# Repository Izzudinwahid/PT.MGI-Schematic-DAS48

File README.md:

# PT.MGI-Schematic-DAS48
Rangkaian Device Alert System 48 Channel 110v

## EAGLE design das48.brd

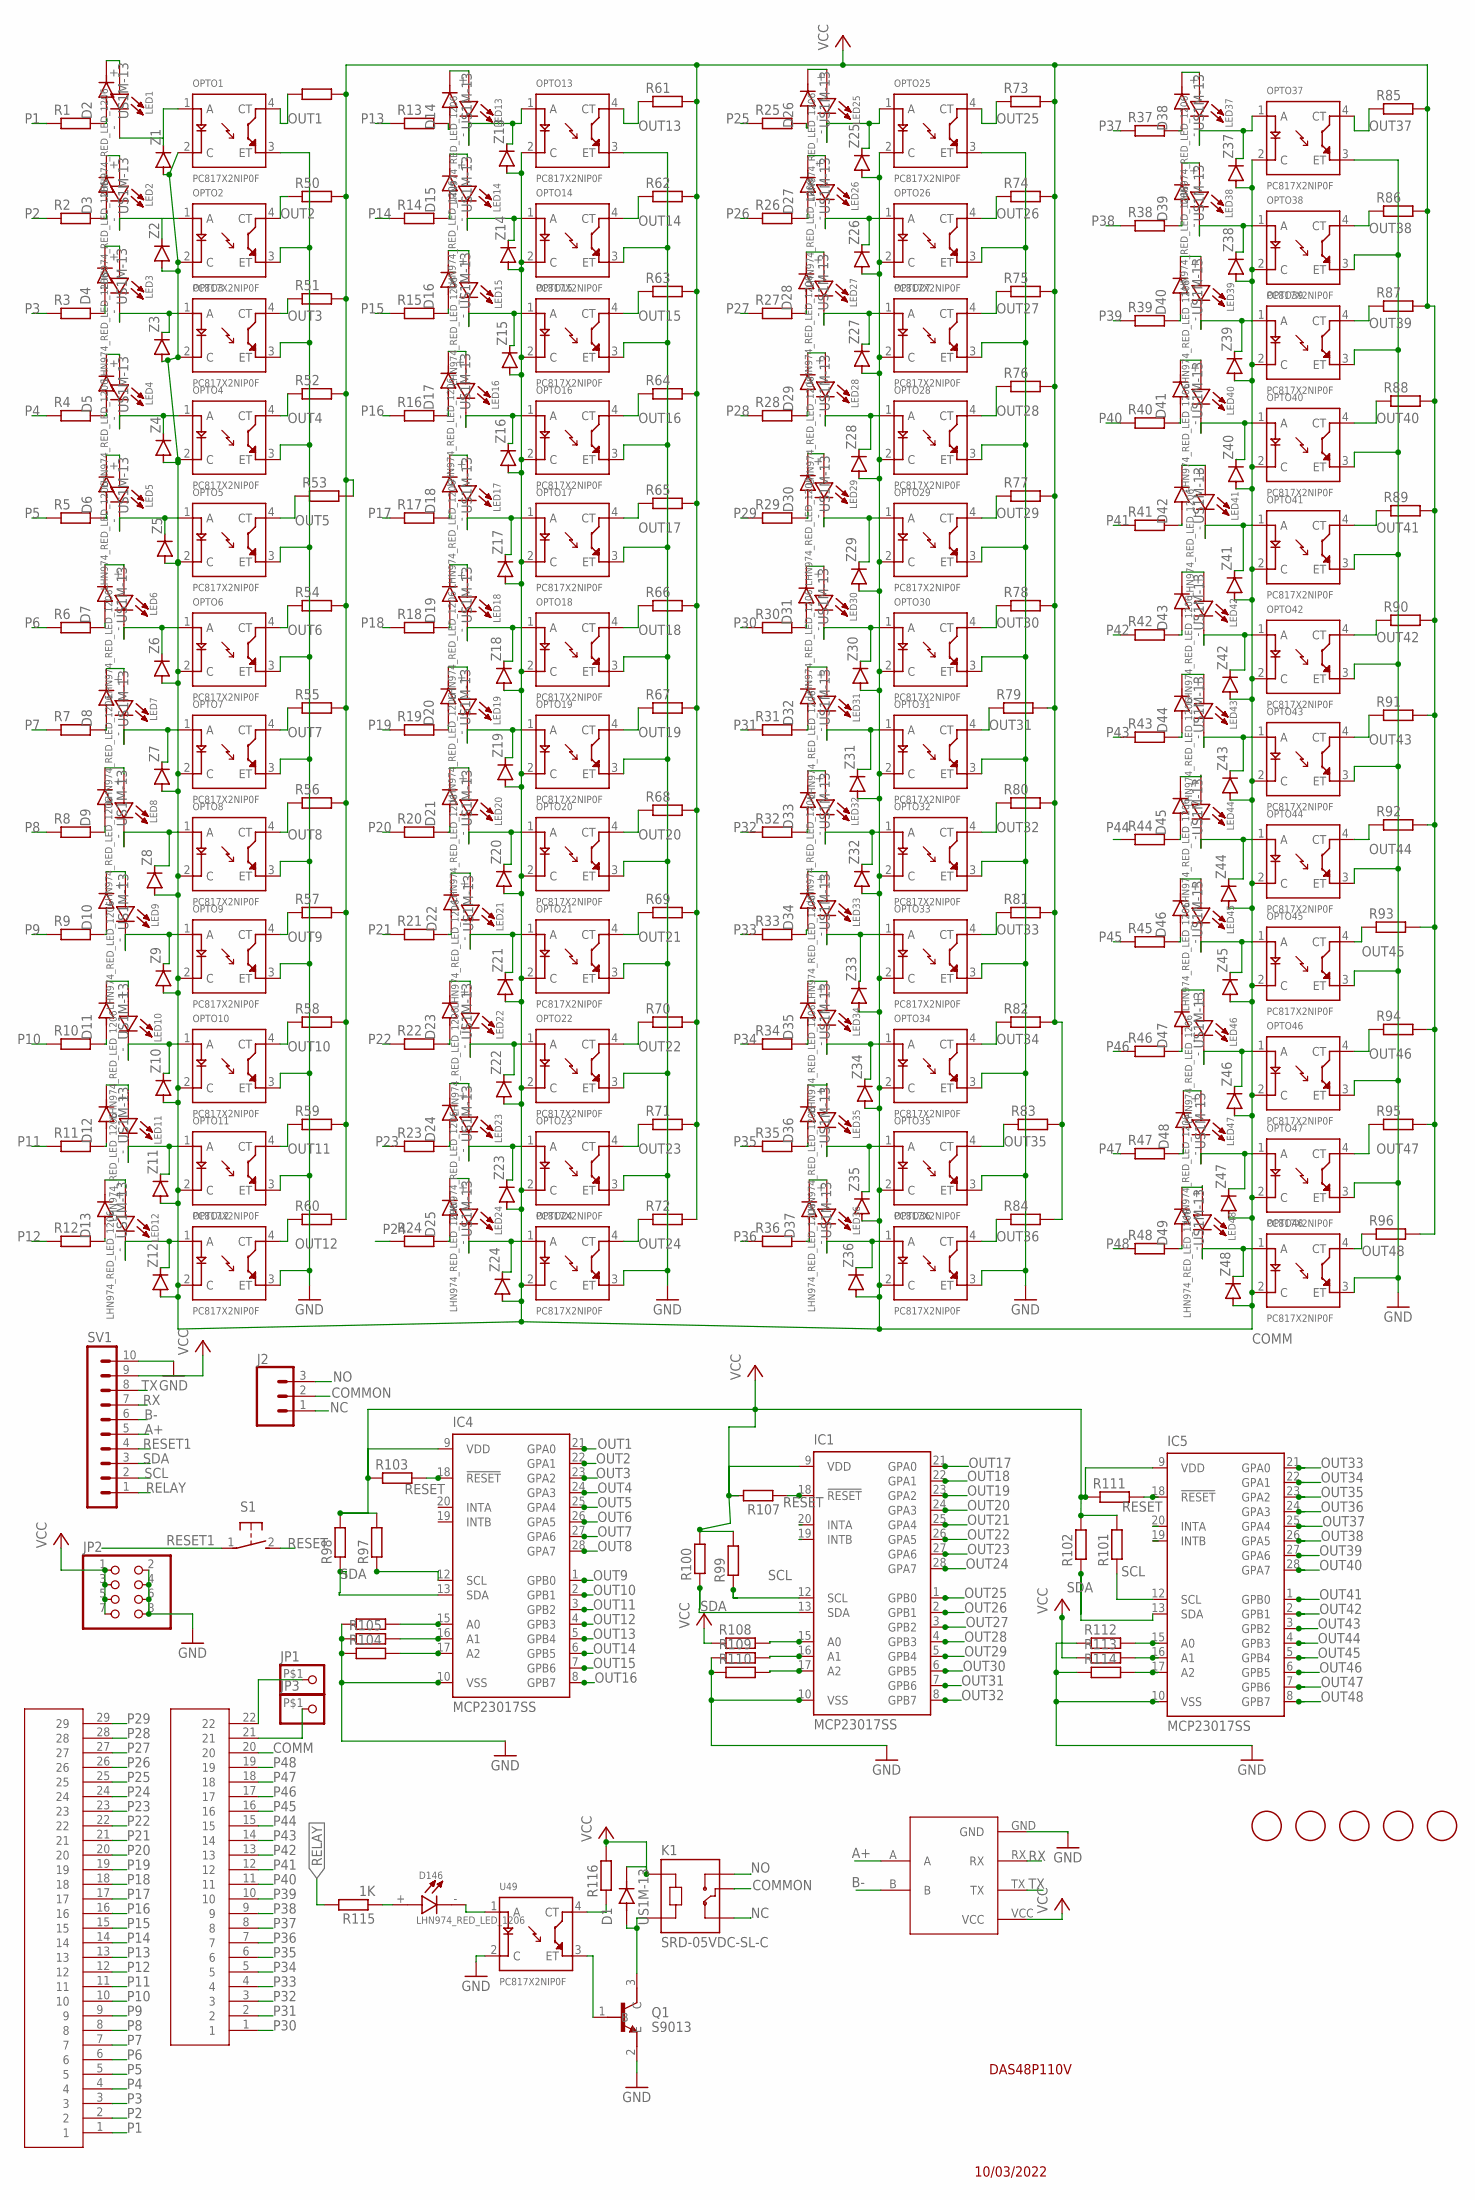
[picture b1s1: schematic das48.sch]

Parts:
D1, D2, D3, D4, D5, D6, D7, D8, D9, D10, D11, D12, D13, D14, D15, D16, D17, D18, D19, D20, D21, D22, D23, D24, D25, D26, D27, D28, D29, D30, D31, D32, D33, D34, D35, D36, D37, D38, D39, D40, D41, D42, D43, D44, D45, D46, D47, D48, D49: US1M-13; DIOM5226X240N
D146: LHN974_RED_LED_1206; LEDC3216X120N
HEADER-22P1: HEADER-22P; HEADER-29P
HEADER-29P1: HEADER-29P
IC1, IC4, IC5: MCP23017SS; SSOP28DB
J2: CONN_03LONGPADS; 1X03_LONGPADS
JP1, JP3: PINHD-1X1-BIGPOGO; 1X1-BIGPOGO
JP2: PINHD-2X4; 2X04
K1: SRD-05VDC-SL-C; RELAY_SRD-05VDC-SL-C
LED1, LED2, LED3, LED4, LED5, LED6, LED7, LED8, LED9, LED10, LED11, LED12, LED13, LED14, LED15, LED16, LED17, LED18, LED19, LED20, LED21, LED22, LED23, LED24, LED25, LED26, LED27, LED28, LED29, LED30, LED31, LED32, LED33, LED34, LED35, LED36, LED37, LED38, LED39, LED40, LED41, LED42, LED43, LED44, LED45, LED46, LED47, LED48: LHN974_RED_LED_1206; LEDC3216X120N
OPTO1, OPTO2, OPTO3, OPTO4, OPTO5, OPTO6, OPTO7, OPTO8, OPTO9, OPTO10, OPTO11, OPTO12, OPTO13, OPTO14, OPTO15, OPTO16, OPTO17, OPTO18, OPTO19, OPTO20, OPTO21, OPTO22, OPTO23, OPTO24, OPTO25, OPTO26, OPTO27, OPTO28, OPTO29, OPTO30, OPTO31, OPTO32, OPTO33, OPTO34, OPTO35, OPTO36, OPTO37, OPTO38, OPTO39, OPTO40, OPTO41, OPTO42, OPTO43, OPTO44, OPTO45, OPTO46, OPTO47, OPTO48: PC817X2NIP0F; SOT254P975X400-4N
Q1: S9013; SOT95P240X120-3N
R1, R2, R3, R4, R5, R6, R7, R8, R9, R10, R11, R12, R13, R14, R15, R16, R17, R18, R19, R20, R21, R22, R23, R24, R25, R26, R27, R28, R29, R30, R31, R32, R33, R34, R35, R36, R37, R38, R39, R40, R41, R42, R43, R44, R45, R46, R47, R48: R-EU_0617/17; 0617/17
R49, R50, R51, R52, R53, R54, R55, R56, R57, R58, R59, R60, R61, R62, R63, R64, R65, R66, R67, R68, R69, R70, R71, R72, R73, R74, R75, R76, R77, R78, R79, R80, R81, R82, R83, R84, R85, R86, R87, R88, R89, R90, R91, R92, R93, R94, R95, R96, R97, R98, R99, R100, R101, R102, R103, R104, R105, R106, R107, R108, R109, R110, R111, R112, R113, R114, R116: R-EU_R0805; R0805
R115: 1K; R0805
S1: 31-XX; B3F-31XX
SV1: MA10-1
TTL-RS1: TTL-RS485
U49: PC817X2NIP0F; SOT254P975X400-4N
U$1, U$2, U$3, U$4, U$5: FIDUCIAL; FIDUCIAL_1MM
Z1, Z2, Z3, Z4, Z5, Z6, Z7, Z8, Z9, Z10, Z11, Z12, Z13, Z14, Z15, Z16, Z17, Z18, Z19, Z20, Z21, Z22, Z23, Z24, Z25, Z26, Z27, Z28, Z29, Z30, Z31, Z32, Z33, Z34, Z35, Z36, Z37, Z38, Z39, Z40, Z41, Z42, Z43, Z44, Z45, Z46, Z47, Z48: DIODE-SOD123; SOD123

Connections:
A+: SV1.5, TTL-RS1.A
B-: SV1.6, TTL-RS1.B
COMM: HEADER-22P1.20, OPTO1.2 (C), OPTO2.2 (C), OPTO3.2 (C), OPTO4.2 (C), OPTO5.2 (C), OPTO6.2 (C), OPTO7.2 (C), OPTO8.2 (C), OPTO9.2 (C), OPTO10.2 (C), OPTO11.2 (C), OPTO12.2 (C), OPTO13.2 (C), OPTO14.2 (C), OPTO15.2 (C), OPTO16.2 (C), OPTO17.2 (C), OPTO18.2 (C), OPTO19.2 (C), OPTO20.2 (C), OPTO21.2 (C), OPTO22.2 (C), OPTO23.2 (C), OPTO24.2 (C), OPTO25.2 (C), OPTO26.2 (C), OPTO27.2 (C), OPTO28.2 (C), OPTO29.2 (C), OPTO30.2 (C), OPTO31.2 (C), OPTO32.2 (C), OPTO33.2 (C), OPTO34.2 (C), OPTO35.2 (C), OPTO36.2 (C), OPTO37.2 (C), OPTO38.2 (C), OPTO39.2 (C), OPTO40.2 (C), OPTO41.2 (C), OPTO42.2 (C), OPTO43.2 (C), OPTO44.2 (C), OPTO45.2 (C), OPTO46.2 (C), OPTO47.2 (C), OPTO48.2 (C), Z1.A, Z2.A, Z3.A, Z4.A, Z5.A, Z6.A, Z7.A, Z8.A, Z9.A, Z10.A, Z11.A, Z12.A, Z13.A, Z14.A, Z15.A, Z16.A, Z17.A, Z18.A, Z19.A, Z20.A, Z21.A, Z22.A, Z23.A, Z24.A, Z25.A, Z26.A, Z27.A, Z28.A, Z29.A, Z30.A, Z31.A, Z32.A, Z33.A, Z34.A, Z35.A, Z36.A, Z37.A, Z38.A, Z39.A, Z40.A, Z41.A, Z42.A, Z43.A, Z44.A, Z45.A, Z46.A, Z47.A, Z48.A
COMMON: J2.2, K1.COM
GND: IC1.10 (VSS), IC4.10 (VSS), IC5.10 (VSS), JP2.2, JP2.4, JP2.6, JP2.8, OPTO1.3 (ET), OPTO2.3 (ET), OPTO3.3 (ET), OPTO4.3 (ET), OPTO5.3 (ET), OPTO6.3 (ET), OPTO7.3 (ET), OPTO8.3 (ET), OPTO9.3 (ET), OPTO10.3 (ET), OPTO11.3 (ET), OPTO12.3 (ET), OPTO13.3 (ET), OPTO14.3 (ET), OPTO15.3 (ET), OPTO16.3 (ET), OPTO17.3 (ET), OPTO18.3 (ET), OPTO19.3 (ET), OPTO20.3 (ET), OPTO21.3 (ET), OPTO22.3 (ET), OPTO23.3 (ET), OPTO24.3 (ET), OPTO25.3 (ET), OPTO26.3 (ET), OPTO27.3 (ET), OPTO28.3 (ET), OPTO29.3 (ET), OPTO30.3 (ET), OPTO31.3 (ET), OPTO32.3 (ET), OPTO33.3 (ET), OPTO34.3 (ET), OPTO35.3 (ET), OPTO36.3 (ET), OPTO37.3 (ET), OPTO38.3 (ET), OPTO39.3 (ET), OPTO40.3 (ET), OPTO41.3 (ET), OPTO42.3 (ET), OPTO43.3 (ET), OPTO44.3 (ET), OPTO45.3 (ET), OPTO46.3 (ET), OPTO47.3 (ET), OPTO48.3 (ET), Q1.2 (E), R104.1, R105.1, R106.1, R109.1, R110.1, R112.1, R114.1, SV1.10, TTL-RS1.GND, U49.2 (C)
unnamed: D2.A, R1.2
unnamed: D2.C (K), LED1.+
unnamed: D3.A, R2.2
unnamed: D3.C (K), LED2.+
unnamed: D4.A, R3.2
unnamed: D4.C (K), LED3.+
unnamed: D5.A, R4.2
unnamed: D5.C (K), LED4.+
unnamed: D6.A, R5.2
unnamed: D6.C (K), LED5.+
unnamed: D7.A, R6.2
unnamed: D7.C (K), LED6.+
unnamed: D8.A, R7.2
unnamed: D8.C (K), LED7.+
unnamed: D9.A, R8.2
unnamed: D9.C (K), LED8.+
unnamed: D15.A, R14.2
unnamed: LED1.-, OPTO1.1 (A), Z1.C
unnamed: LED13.-, OPTO13.1 (A), Z13.C
unnamed: D10.A, R9.2
unnamed: LED14.-, OPTO14.1 (A), Z14.C
unnamed: D10.C (K), LED9.+
unnamed: LED15.-, OPTO15.1 (A), Z15.C
unnamed: D11.A, R10.2
unnamed: LED16.-, OPTO16.1 (A), Z16.C
unnamed: D11.C (K), LED10.+
unnamed: LED17.-, OPTO17.1 (A), Z17.C
unnamed: D12.A, R11.2
unnamed: LED18.-, OPTO18.1 (A), Z18.C
unnamed: D12.C (K), LED11.+
unnamed: LED19.-, OPTO19.1 (A), Z19.C
unnamed: LED20.-, OPTO20.1 (A), Z20.C
unnamed: LED21.-, OPTO21.1 (A), Z21.C
unnamed: D15.C (K), LED14.+
unnamed: LED22.-, OPTO22.1 (A), Z22.C
unnamed: D13.A, R12.2
unnamed: LED23.-, OPTO23.1 (A), Z23.C
unnamed: D13.C (K), LED12.+
unnamed: LED24.-, OPTO24.1 (A), Z24.C
unnamed: D14.A, R13.2
unnamed: LED25.-, OPTO25.1 (A), Z25.C
unnamed: D14.C (K), LED13.+
unnamed: LED26.-, OPTO26.1 (A), Z26.C
unnamed: D16.A, R15.2
unnamed: LED27.-, OPTO27.1 (A), Z27.C
unnamed: D16.C (K), LED15.+
unnamed: LED28.-, OPTO28.1 (A), Z28.C
unnamed: D17.A, R16.2
unnamed: LED29.-, OPTO29.1 (A), Z29.C
unnamed: D17.C (K), LED16.+
unnamed: LED30.-, OPTO30.1 (A), Z30.C
unnamed: D18.A, R17.2
unnamed: LED31.-, OPTO31.1 (A), Z31.C
unnamed: D18.C (K), LED17.+
unnamed: LED32.-, OPTO32.1 (A), Z32.C
unnamed: D19.A, R18.2
unnamed: LED33.-, OPTO33.1 (A), Z33.C
unnamed: D19.C (K), LED18.+
unnamed: LED34.-, OPTO34.1 (A), Z34.C
unnamed: D20.A, R19.2
unnamed: LED35.-, OPTO35.1 (A), Z35.C
unnamed: D20.C (K), LED19.+
unnamed: LED36.-, OPTO36.1 (A), Z36.C
unnamed: D32.A, R31.2
unnamed: LED37.-, OPTO37.1 (A), Z37.C
unnamed: D21.A, R20.2
unnamed: LED38.-, OPTO38.1 (A), Z38.C
unnamed: D21.C (K), LED20.+
unnamed: LED39.-, OPTO39.1 (A), Z39.C
unnamed: LED40.-, OPTO40.1 (A), Z40.C
unnamed: D22.A, R21.2
unnamed: LED41.-, OPTO41.1 (A), Z41.C
unnamed: D22.C (K), LED21.+
unnamed: LED42.-, OPTO42.1 (A), Z42.C
unnamed: LED43.-, OPTO43.1 (A), Z43.C
unnamed: D23.A, R22.2
unnamed: LED44.-, OPTO44.1 (A), Z44.C
unnamed: D23.C (K), LED22.+
unnamed: LED45.-, OPTO45.1 (A), Z45.C
unnamed: D24.A, R23.2
unnamed: LED46.-, OPTO46.1 (A), Z46.C
unnamed: D24.C (K), LED23.+
unnamed: LED47.-, OPTO47.1 (A), Z47.C
unnamed: D25.A, R24.2
unnamed: LED48.-, OPTO48.1 (A), Z48.C
unnamed: LED2.-, OPTO2.1 (A), Z2.C
unnamed: LED3.-, OPTO3.1 (A), Z3.C
unnamed: LED4.-, OPTO4.1 (A), Z4.C
unnamed: LED5.-, OPTO5.1 (A), Z5.C
unnamed: LED6.-, OPTO6.1 (A), Z6.C
unnamed: LED7.-, OPTO7.1 (A), Z7.C
unnamed: LED8.-, OPTO8.1 (A), Z8.C
unnamed: LED9.-, OPTO9.1 (A), Z9.C
unnamed: LED10.-, OPTO10.1 (A), Z10.C
unnamed: LED11.-, OPTO11.1 (A), Z11.C
unnamed: LED12.-, OPTO12.1 (A), Z12.C
unnamed: D146.-, U49.1 (A)
unnamed: D146.+, R115.1
unnamed: R116.1, U49.4 (CT)
unnamed: IC5.15 (A0), R112.2
unnamed: D1.A, K1.A2, Q1.3 (C)
unnamed: Q1.1 (B), U49.3 (ET)
unnamed: IC5.16 (A1), R113.2
unnamed: D25.C (K), LED24.+
unnamed: D26.A, R25.2
unnamed: D26.C (K), LED25.+
unnamed: IC1.15 (A0), R108.2
unnamed: IC1.16 (A1), R109.2
unnamed: IC4.15 (A0), R106.2
unnamed: IC4.16 (A1), R105.2
unnamed: IC4.17 (A2), R104.2
unnamed: IC5.17 (A2), R114.2
unnamed: IC1.17 (A2), R110.2
unnamed: D27.A, R26.2
unnamed: D27.C (K), LED26.+
unnamed: D28.A, R27.2
unnamed: D28.C (K), LED27.+
unnamed: D32.C (K), LED31.+
unnamed: D29.A, R28.2
unnamed: D29.C (K), LED28.+
unnamed: D30.C (K), LED29.+
unnamed: D30.A, R29.2
unnamed: D31.A, R30.2
unnamed: D31.C (K), LED30.+
unnamed: D33.C (K), LED32.+
unnamed: D33.A, R32.2
unnamed: D35.A, R34.2
unnamed: D35.C (K), LED34.+
unnamed: D36.A, R35.2
unnamed: D36.C (K), LED35.+
unnamed: D42.A, R41.2
unnamed: D37.A, R36.2
unnamed: D37.C (K), LED36.+
unnamed: D38.A, R37.2
unnamed: D34.A, R33.2
unnamed: D34.C (K), LED33.+
unnamed: D38.C (K), LED37.+
unnamed: D39.A, R38.2
unnamed: D39.C (K), LED38.+
unnamed: D40.A, R39.2
unnamed: D40.C (K), LED39.+
unnamed: D41.A, R40.2
unnamed: D41.C (K), LED40.+
unnamed: D42.C (K), LED41.+
unnamed: D43.A, R42.2
unnamed: D43.C (K), LED42.+
unnamed: D44.A, R43.2
unnamed: D44.C (K), LED43.+
unnamed: D45.A, R44.2
unnamed: D45.C (K), LED44.+
unnamed: D46.A, R45.2
unnamed: D46.C (K), LED45.+
unnamed: D47.A, R46.2
unnamed: D47.C (K), LED46.+
unnamed: D48.C (K), LED47.+
unnamed: HEADER-22P1.21, JP3.P$1
unnamed: HEADER-22P1.22, JP1.P$1
unnamed: D48.A, R47.2
unnamed: D49.A, R48.2
unnamed: D49.C (K), LED48.+
NC: J2.1, K1.NC
NO: J2.3, K1.NO
OUT1: IC4.21 (GPA0), OPTO1.4 (CT), R49.1
OUT2: IC4.22 (GPA1), OPTO2.4 (CT), R50.1
OUT3: IC4.23 (GPA2), OPTO3.4 (CT), R51.1
OUT4: IC4.24 (GPA3), OPTO4.4 (CT), R52.1
OUT5: IC4.25 (GPA4), OPTO5.4 (CT), R53.1
OUT6: IC4.26 (GPA5), OPTO6.4 (CT), R54.1
OUT7: IC4.27 (GPA6), OPTO7.4 (CT), R55.1
OUT8: IC4.28 (GPA7), OPTO8.4 (CT), R56.1
OUT9: IC4.1 (GPB0), OPTO9.4 (CT), R57.1
OUT10: IC4.2 (GPB1), OPTO10.4 (CT), R58.1
OUT11: IC4.3 (GPB2), OPTO11.4 (CT), R59.1
OUT12: IC4.4 (GPB3), OPTO12.4 (CT), R60.1
OUT13: IC4.5 (GPB4), OPTO13.4 (CT), R61.1
OUT14: IC4.6 (GPB5), OPTO14.4 (CT), R62.1
OUT15: IC4.7 (GPB6), OPTO15.4 (CT), R63.1
OUT16: IC4.8 (GPB7), OPTO16.4 (CT), R64.1
OUT17: IC1.21 (GPA0), OPTO17.4 (CT), R65.1
OUT18: IC1.22 (GPA1), OPTO18.4 (CT), R66.1
OUT19: IC1.23 (GPA2), OPTO19.4 (CT), R67.1
OUT20: IC1.24 (GPA3), OPTO20.4 (CT), R68.1
OUT21: IC1.25 (GPA4), OPTO21.4 (CT), R69.1
OUT22: IC1.26 (GPA5), OPTO22.4 (CT), R70.1
OUT23: IC1.27 (GPA6), OPTO23.4 (CT), R71.1
OUT24: IC1.28 (GPA7), OPTO24.4 (CT), R72.1
OUT25: IC1.1 (GPB0), OPTO25.4 (CT), R73.1
OUT26: IC1.2 (GPB1), OPTO26.4 (CT), R74.1
OUT27: IC1.3 (GPB2), OPTO27.4 (CT), R75.1
OUT28: IC1.4 (GPB3), OPTO28.4 (CT), R76.1
OUT29: IC1.5 (GPB4), OPTO29.4 (CT), R77.1
OUT30: IC1.6 (GPB5), OPTO30.4 (CT), R78.1
OUT31: IC1.7 (GPB6), OPTO31.4 (CT), R79.1
OUT32: IC1.8 (GPB7), OPTO32.4 (CT), R80.1
OUT33: IC5.21 (GPA0), OPTO33.4 (CT), R81.1
OUT34: IC5.22 (GPA1), OPTO34.4 (CT), R82.1
OUT35: IC5.23 (GPA2), OPTO35.4 (CT), R83.1
OUT36: IC5.24 (GPA3), OPTO36.4 (CT), R84.1
OUT37: IC5.25 (GPA4), OPTO37.4 (CT), R85.1
OUT38: IC5.26 (GPA5), OPTO38.4 (CT), R86.1
OUT39: IC5.27 (GPA6), OPTO39.4 (CT), R87.1
OUT40: IC5.28 (GPA7), OPTO40.4 (CT), R88.1
OUT41: IC5.1 (GPB0), OPTO41.4 (CT), R89.1
OUT42: IC5.2 (GPB1), OPTO42.4 (CT), R90.1
OUT43: IC5.3 (GPB2), OPTO43.4 (CT), R91.1
OUT44: IC5.4 (GPB3), OPTO44.4 (CT), R92.1
OUT45: IC5.5 (GPB4), OPTO45.4 (CT), R93.1
OUT46: IC5.6 (GPB5), OPTO46.4 (CT), R94.1
OUT47: IC5.7 (GPB6), OPTO47.4 (CT), R95.1
OUT48: IC5.8 (GPB7), OPTO48.4 (CT), R96.1
P1: HEADER-29P1.1, R1.1
P2: HEADER-29P1.2, R2.1
P3: HEADER-29P1.3, R3.1
P4: HEADER-29P1.4, R4.1
P5: HEADER-29P1.5, R5.1
P6: HEADER-29P1.6, R6.1
P7: HEADER-29P1.7, R7.1
P8: HEADER-29P1.8, R8.1
P9: HEADER-29P1.9, R9.1
P10: HEADER-29P1.10, R10.1
P11: HEADER-29P1.11, R11.1
P12: HEADER-29P1.12, R12.1
P13: HEADER-29P1.13, R13.1
P14: HEADER-29P1.14, R14.1
P15: HEADER-29P1.15, R15.1
P16: HEADER-29P1.16, R16.1
P17: HEADER-29P1.17, R17.1
P18: HEADER-29P1.18, R18.1
P19: HEADER-29P1.19, R19.1
P20: HEADER-29P1.20, R20.1
P21: HEADER-29P1.21, R21.1
P22: HEADER-29P1.22, R22.1
P23: HEADER-29P1.23, R23.1
P24: HEADER-29P1.24, R24.1
P25: HEADER-29P1.25, R25.1
P26: HEADER-29P1.26, R26.1
P27: HEADER-29P1.27, R27.1
P28: HEADER-29P1.28, R28.1
P29: HEADER-29P1.29, R29.1
P30: HEADER-22P1.1, R30.1
P31: HEADER-22P1.2, R31.1
P32: HEADER-22P1.3, R32.1
P33: HEADER-22P1.4, R33.1
P34: HEADER-22P1.5, R34.1
P35: HEADER-22P1.6, R35.1
P36: HEADER-22P1.7, R36.1
P37: HEADER-22P1.8, R37.1
P38: HEADER-22P1.9, R38.1
P39: HEADER-22P1.10, R39.1
P40: HEADER-22P1.11, R40.1
P41: HEADER-22P1.12, R41.1
P42: HEADER-22P1.13, R42.1
P43: HEADER-22P1.14, R43.1
P44: HEADER-22P1.15, R44.1
P45: HEADER-22P1.16, R45.1
P46: HEADER-22P1.17, R46.1
P47: HEADER-22P1.18, R47.1
P48: HEADER-22P1.19, R48.1
RELAY: R115.2, SV1.1
RESET: IC1.18 (!RESET), IC4.18 (!RESET), IC5.18 (!RESET), R103.2, R107.1, R111.2, S1.2 (S)
RESET1: S1.1, SV1.4
RX: SV1.7, TTL-RS1.RX
SCL: IC1.12 (SCL), IC4.12 (SCL), IC5.12 (SCL), R97.1, R99.1, R101.1, SV1.2
SDA: IC1.13 (SDA), IC4.13 (SDA), IC5.13 (SDA), R98.1, R100.1, R102.1, SV1.3
TX: SV1.8, TTL-RS1.TX
VCC: D1.C (K), IC1.9 (VDD), IC4.9 (VDD), IC5.9 (VDD), JP2.1, JP2.3, JP2.5, JP2.7, K1.A1, R49.2, R50.2, R51.2, R52.2, R53.2, R54.2, R55.2, R56.2, R57.2, R58.2, R59.2, R60.2, R61.2, R62.2, R63.2, R64.2, R65.2, R66.2, R67.2, R68.2, R69.2, R70.2, R71.2, R72.2, R73.2, R74.2, R75.2, R76.2, R77.2, R78.2, R79.2, R80.2, R81.2, R82.2, R83.2, R84.2, R85.2, R86.2, R87.2, R88.2, R89.2, R90.2, R91.2, R92.2, R93.2, R94.2, R95.2, R96.2, R97.2, R98.2, R99.2, R100.2, R101.2, R102.2, R103.1, R107.2, R108.1, R111.1, R113.1, R116.2, SV1.9, TTL-RS1.VCC

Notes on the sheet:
DAS48P110V
10/03/2022

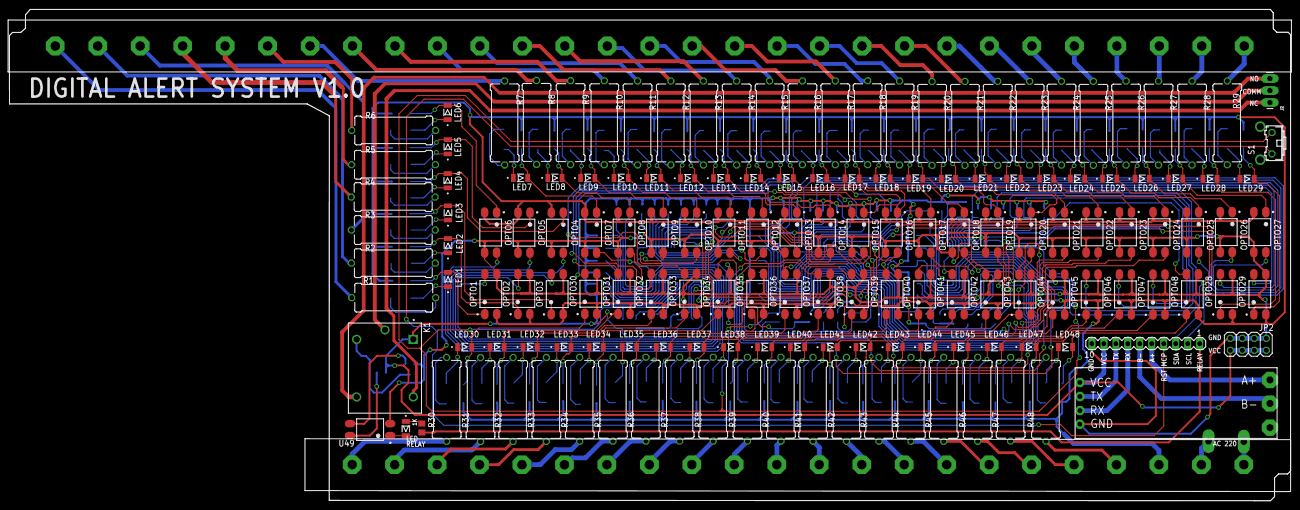
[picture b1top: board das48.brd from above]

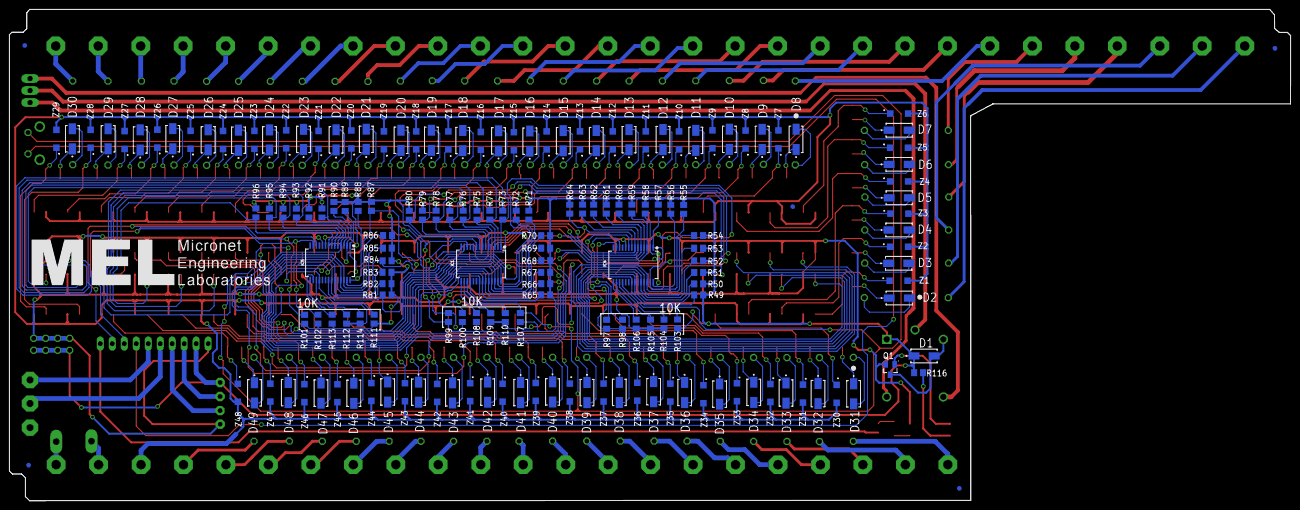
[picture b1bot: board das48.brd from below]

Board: 2 copper layers, 271.5 x 104.1 mm, 330 parts (173 on the bottom side), 271 nets.

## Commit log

2022-08-10 Menambahkan File .sch dan .brd
2023-06-07 update
    remove scl-sda jumper
    fixing label

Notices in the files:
parts and their libraries:
SparkFun-Connectors: Licensing: Creative Commons ShareAlike 4.0 International - https://creativecommons.org/licenses/by-sa/4.0
